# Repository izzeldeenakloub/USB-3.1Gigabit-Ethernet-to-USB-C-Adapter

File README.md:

# HelloBoardPCB

A KiCad design project for a **USB-C to Gigabit Ethernet adapter** and my first complete 4-layer PCB layout.

## Project Purpose

This project was created as a proof of concept to practice:

- Four-layer PCB stack-up design
- USB-C connector integration
- Gigabit Ethernet routing and component placement
- Ground and power plane organization
- Differential-pair placement and routing
- KiCad schematic and PCB layout workflows

## Current Status

The schematic and initial PCB placement/routing have been completed.

However, this revision is **not production-ready** and has not been fabricated or electrically tested. Some Design Rule Check errors remain because the initial layout was completed before properly configuring:

- PCB manufacturer design constraints
- Net classes
- Differential-pair rules
- Track widths and clearances
- Via sizes
- Controlled-impedance requirements

The current revision should therefore be treated as a **layout study and proof-of-concept design**, rather than a validated manufacturing release.

A revised version with properly configured constraints, corrected DRC issues, and manufacturing files is planned.

## Current Schematic

## Current PCB Layout

## Planned Improvements

- Configure manufacturer-specific design rules
- Create dedicated USB 2.0, USB 3.x, Ethernet, power, and general-signal net classes
- Set appropriate differential-pair widths and spacing
- Review high-speed signal return paths
- Correct remaining ERC and DRC violations
- Review grounding and chassis/Earth connections
- Generate Gerber, drill, BOM, and pick-and-place files
- Perform a final manufacturability review

## Tools

- KiCad
- Four-layer PCB stack-up:
  - Front copper: components and signals
  - Inner layer 1: ground plane
  - Inner layer 2: power distribution
  - Back copper: signals

## Disclaimer

This repository currently documents my PCB design and learning process. The board should not be manufactured from the current files without completing a full electrical, mechanical, signal-integrity, and design-rule review.

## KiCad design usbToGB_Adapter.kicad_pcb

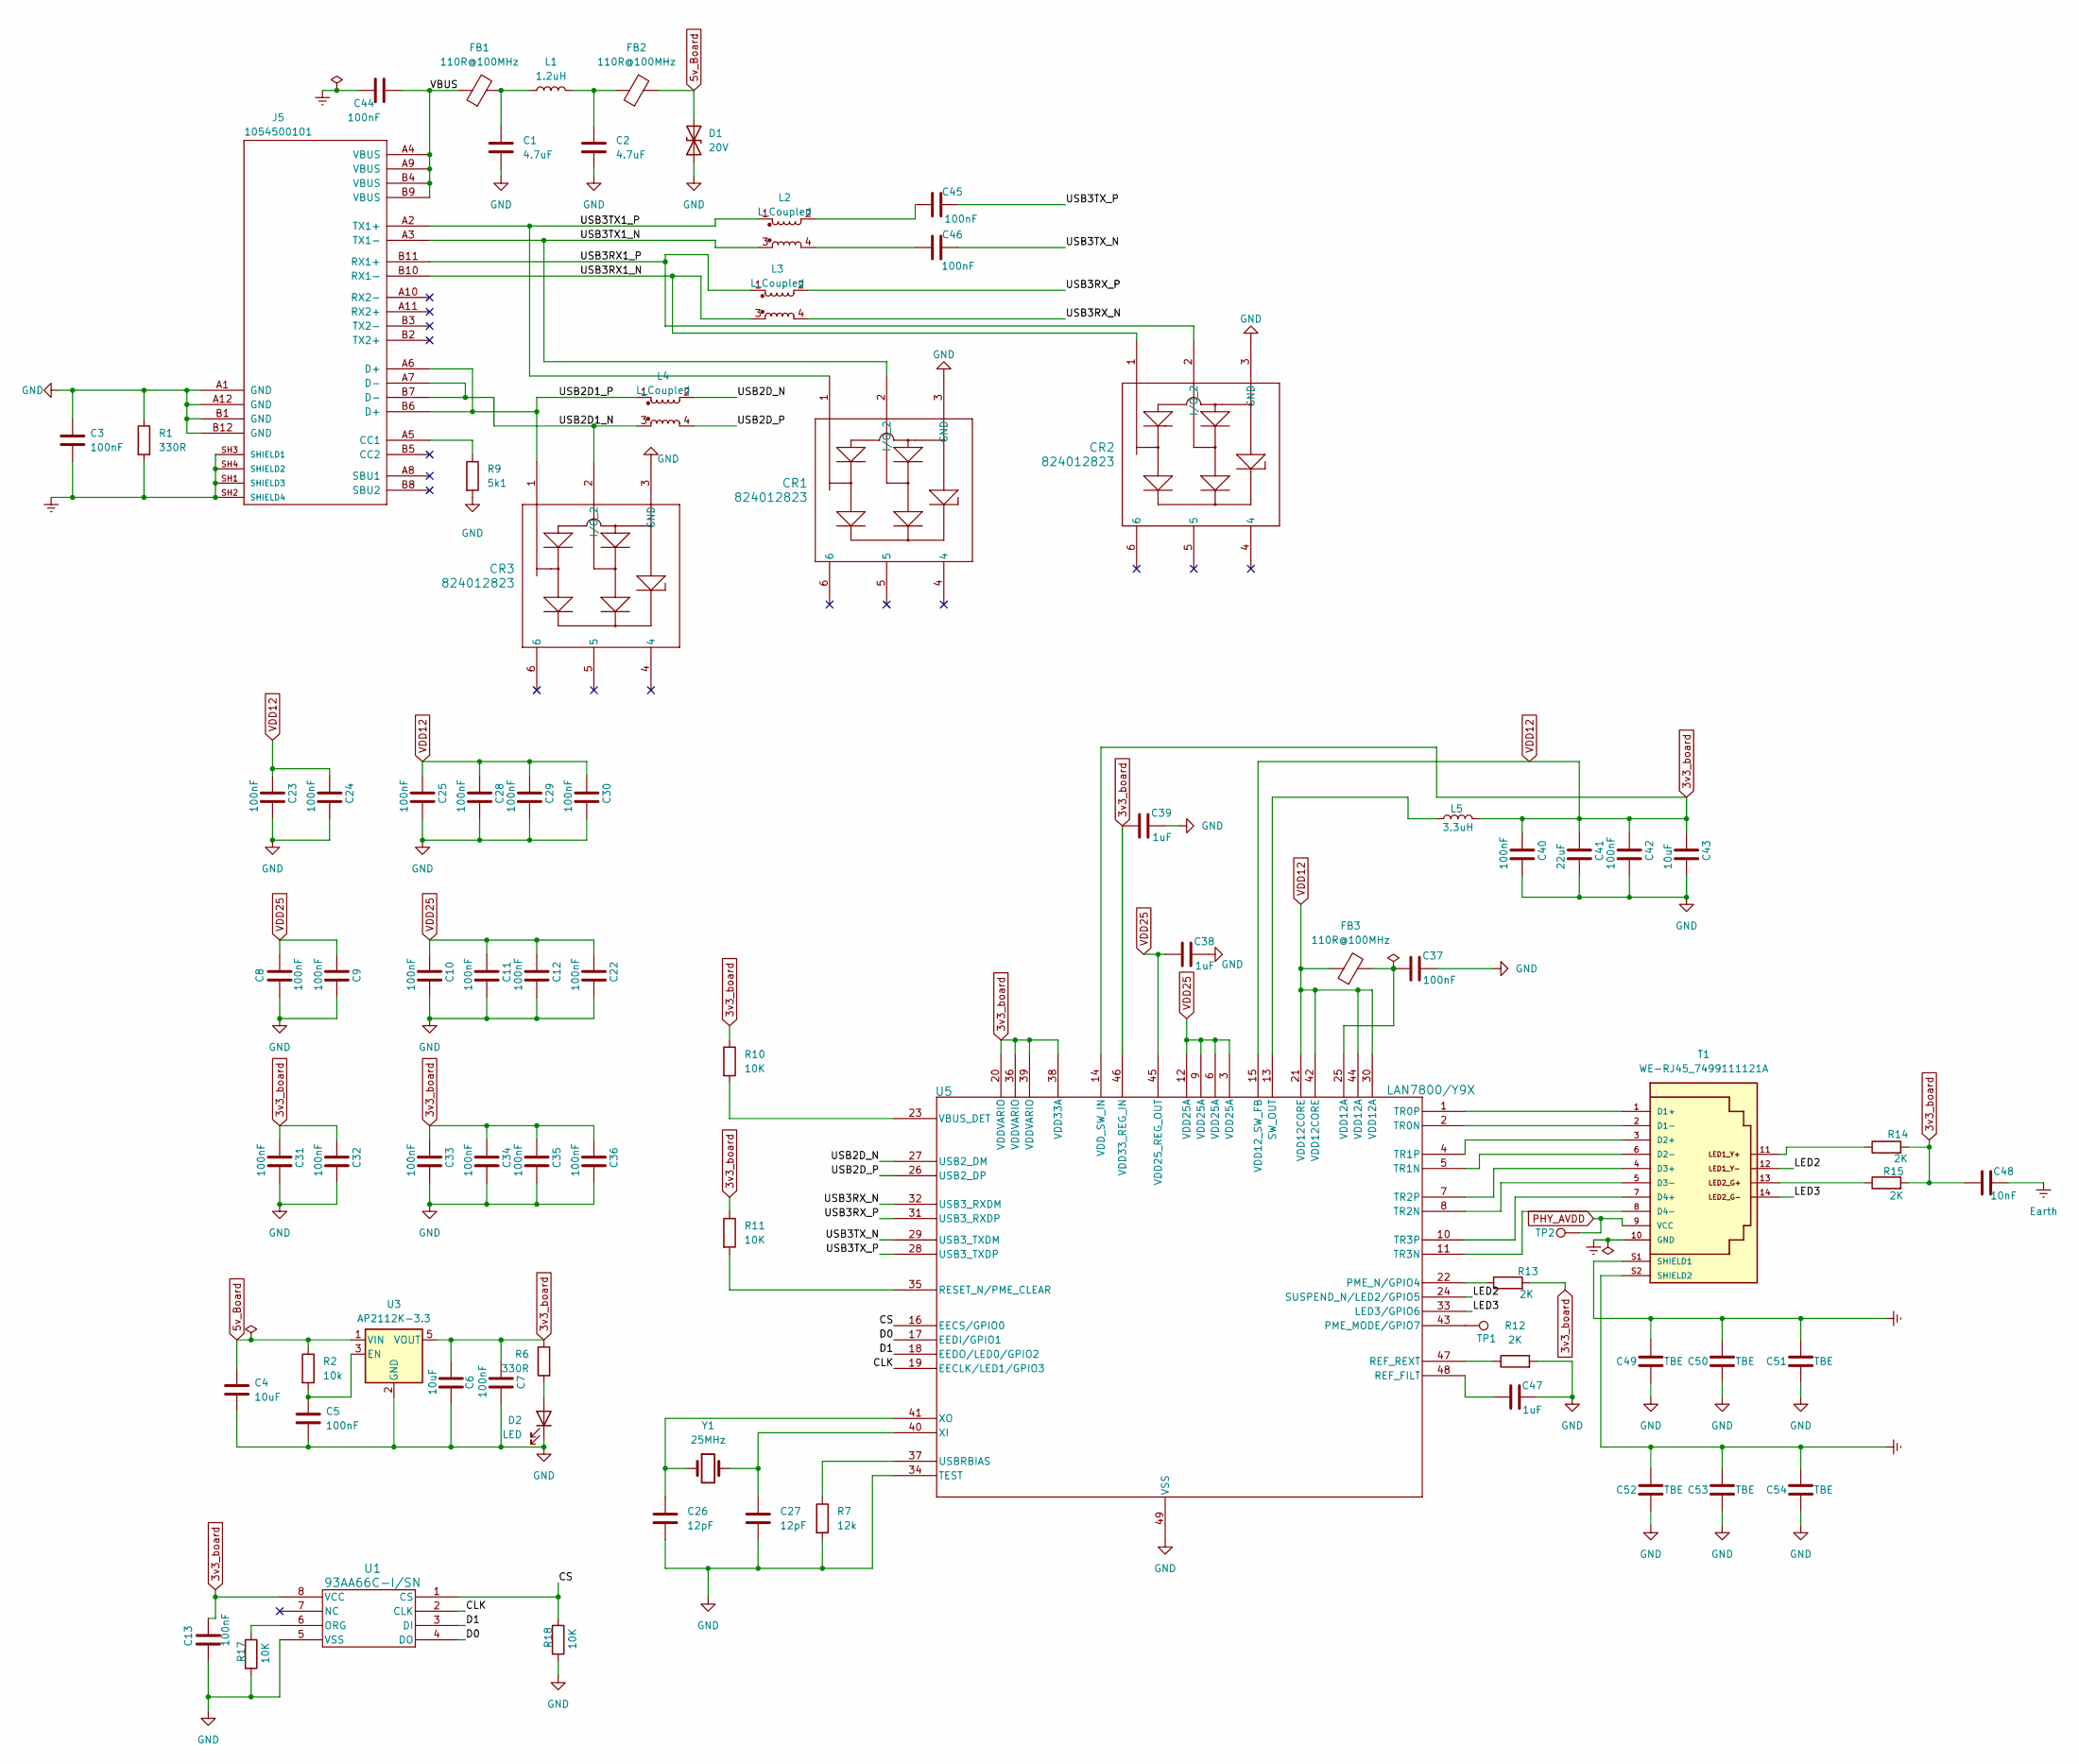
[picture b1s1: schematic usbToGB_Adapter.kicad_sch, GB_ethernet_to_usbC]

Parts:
C1, C2: 4.7uF; C_0805_2012Metric
C3, C8, C9, C10, C11, C12, C13, C22, C23, C24, C25, C28, C29, C30, C31, C32, C33, C34, C35, C36, C37, C40, C42: 100nF; C_0603_1608Metric
C4, C6, C43: 10uF; C_0805_2012Metric
C5, C7, C44: 100nF; C_0805_2012Metric
C26, C27: 12pF; C_0603_1608Metric
C38, C39, C47: 1uF; C_0603_1608Metric
C41: 22uF; C_0805_2012Metric
C45, C46: 100nF; C_0402_1005Metric
C48: 10nF; C_0603_1608Metric
C49, C52: TBE; C_1210_3225Metric
C50, C51, C53, C54: TBE; C_1206_3216Metric
CR1, CR2, CR3: 824012823; DFN_012823_WRE
D1: 20V; C_0805_2012Metric
D2: LED; LED_0603_1608Metric
FB1, FB2: 110R@100MHz; L_1206_3216Metric
FB3: 110R@100MHz; L_0603_1608Metric
J5: 1054500101; MOLEX_1054500101; PARTREV A7
L1: 1.2uH; IND_WE-MAPI_3020_WRE
L2, L3: L_Coupled; CHIP_35600_WRE
L4: L_Coupled; SMT_32090_WRE
L5: 3.3uH; IND_WE-LQS_3015_WRE
R1, R6: 330R; R_0603_1608Metric
R2: 10k; R_0603_1608Metric
R7: 12k; R_0603_1608Metric
R9: 5k1; R_0603_1608Metric
R10, R11, R17, R18: 10K; R_0603_1608Metric
R12, R13, R14, R15: 2K; R_0603_1608Metric
T1: WE-RJ45_7499111121A; 7499111121A
TP1, TP2: TestPoint; TestPoint_Pad_D2.0mm
U1: 93AA66C-I/SN; SOIC8-N_MC_MCH
U3: AP2112K-3.3; SOT-23-5
U5: LAN7800/Y9X; SQFN48_7X7_Y9X_MCH
Y1: 25MHz; Crystal_SMD_3225-4Pin_3.2x2.5mm_HandSoldering

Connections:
5v_Board: C4.1, D1.2 (A2), FB2.2, R2.1, U3.1 (VIN)
/CLK: U1.2 (CLK), U5.19 (EECLK/LED1/GPIO3)
/CS: R18.1, U1.1 (CS), U5.16 (EECS/GPIO0)
/D0: U1.4 (DO), U5.17 (EEDI/GPIO1)
/D1: U1.3 (DI), U5.18 (EEDO/LED0/GPIO2)
/LED2: T1.12, U5.24 (SUSPEND_N/LED2/GPIO5)
/LED3: T1.14, U5.33 (LED3/GPIO6)
/USB2D1_N: CR3.2 (I/O_2), J5.A7 (D-), J5.B7 (D-), L4.3
/USB2D1_P: CR3.1, J5.A6 (D+), J5.B6 (D+), L4.1
/USB2D_N: L4.2, U5.27 (USB2_DM)
/USB2D_P: L4.4, U5.26 (USB2_DP)
/USB3RX1_N: CR2.1, J5.B10 (RX1-), L3.3
/USB3RX1_P: CR2.2 (I/O_2), J5.B11 (RX1+), L3.1
/USB3RX_N: L3.4, U5.32 (USB3_RXDM)
/USB3RX_P: L3.2, U5.31 (USB3_RXDP)
/USB3TX1_N: CR1.2 (I/O_2), J5.A3 (TX1-), L2.3
/USB3TX1_P: CR1.1, J5.A2 (TX1+), L2.1
/USB3TX_N: C46.1, U5.29 (USB3_TXDM)
/USB3TX_P: C45.1, U5.28 (USB3_TXDP)
/VBUS: C44.2, FB1.1, J5.A4 (VBUS), J5.A9 (VBUS), J5.B4 (VBUS), J5.B9 (VBUS)
<NO NET>: T1.10 (GND)
Earth: C3.2, C44.1, C48.2, C49.2, C50.2, C51.2, C52.2, C53.2, C54.2, J5.SH1 (SHIELD3), J5.SH2 (SHIELD4), J5.SH3 (SHIELD1), J5.SH4 (SHIELD2), R1.2, T1.S1 (SHIELD1), T1.S2 (SHIELD2)
unnamed: C1.2, FB1.2, L1.1
unnamed: C2.2, FB2.1, L1.2
unnamed: C37.1, FB3.2, U5.25 (VDD12A)
unnamed: C45.2, L2.2
unnamed: C46.2, L2.4
unnamed: D2.2 (A), R6.2
unnamed: J5.A5 (CC1), R9.1
unnamed: R14.1, T1.11
unnamed: R15.1, T1.13
unnamed: T1.1 (D1+), U5.1 (TR0P)
unnamed: T1.2 (D1-), U5.2 (TR0N)
unnamed: T1.3 (D2+), U5.4 (TR1P)
unnamed: T1.6 (D2-), U5.5 (TR1N)
unnamed: T1.4 (D3+), U5.7 (TR2P)
unnamed: T1.5 (D3-), U5.8 (TR2N)
unnamed: T1.7 (D4+), U5.10 (TR3P)
unnamed: T1.8 (D4-), U5.11 (TR3N)
unnamed: R17.1, U1.6 (ORG)
unnamed: C5.1, R2.2, U3.3 (EN)
unnamed: TP1.1 (1_1), U5.43 (PME_MODE/GPIO7)
unnamed: R13.1, U5.22 (PME_N/GPIO4)
unnamed: C47.1, U5.48 (REF_FILT)
unnamed: R12.1, U5.47 (REF_REXT)
unnamed: R11.2, U5.35 (RESET_N/PME_CLEAR)
unnamed: L5.1, U5.13 (SW_OUT)
unnamed: R7.1, U5.37 (USBRBIAS)
unnamed: R10.2, U5.23 (VBUS_DET)
unnamed: C27.1, U5.40 (XI), Y1.2
unnamed: C26.1, U5.41 (XO), Y1.1
PHY_AVDD: T1.9 (VCC), TP2.1 (1_1)

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
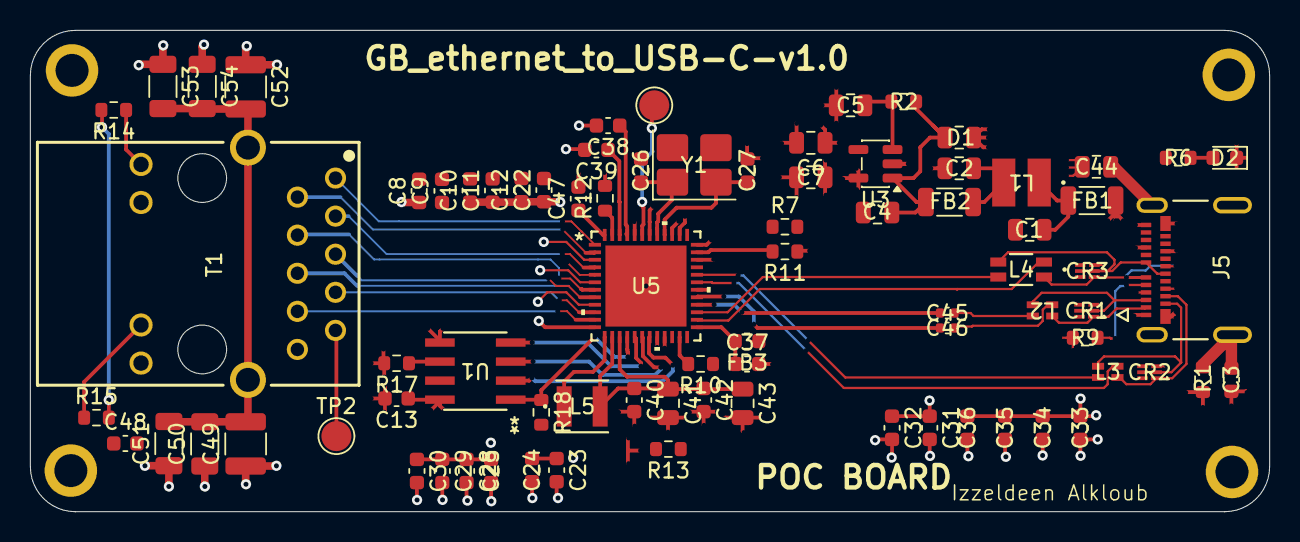
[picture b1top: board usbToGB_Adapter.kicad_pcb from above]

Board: 4 copper layers, 82.7 x 32.1 mm, 80 parts (0 on the bottom side), 54 nets.
